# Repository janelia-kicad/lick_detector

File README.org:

# Created 2021-05-13 Thu 11:52
#+OPTIONS: title:nil author:nil email:nil toc:t |:t ^:nil
* Repository Information

- Name :: lick_detector
- Version :: 1.0
- License :: Open-Source Hardware
- URL :: https://github.com/janelia-kicad/lick_detector
- Author :: Peter Polidoro
- Email :: peter@polidoro.io

** Description

This board was designed to detect mouse licks using an accelerometer. The
board needs to be small and light weight and mounted to a lickport tube that
allows some small amount of motion.

* Images

* Schematic

[[file:./schematic/lick_detector.pdf][./schematic/lick_detector.pdf]]

[[file:./schematic/images/schematic00.png]]

* Gerbers

[[file:./gerbers/images/gerbers00.png]]

[[file:./gerbers/images/gerbers01.png]]

* Bill of Materials

** PCB Parts

| Item | Reference(s) | Quantity | Manufacturer       | Manufacturer Part Number | Vendor   | Vendor Part Number    | Description                  | Package |
|------+--------------+----------+--------------------+--------------------------+----------+-----------------------+------------------------------+---------|
|    1 | C1           |        1 | AVX Corporation    | TLCK106M006QTA           | Digi-Key | 478-5343-1-ND         | CAP TANT 10UF 20% 6.3V       |    0402 |
|    2 | C2 C3        |        2 | TDK Corporation    | C0603X5R1E104K030BB      | Digi-Key | 445-13671-1-ND        | CAP CER 0.1UF 25V X5R        |    0201 |
|    3 | P1           |        1 | Molex              | 5034800800               | Digi-Key | WM1388CT-ND           | CONN FFC FPC 8POS 0.50MM R/A |         |
|    4 | R1           |        1 | Yageo              | RC0201JR-0710RL          | Digi-Key | 311-10NCT-ND          | RES SMD 10 OHM 5% 1/20W      |    0201 |
|    5 | U1           |        1 | Analog Devices Inc | ADXL313WACPZ-RL7         | Digi-Key | ADXL313WACPZ-RL7CT-ND | ACCEL 0.5-4G I2C/SPI 32LFCSP |         |
|      | FID1         |        1 |                    |                          |          |                       |                              |         |

** Supplemental Parts

| Item | Quantity | Manufacturer | Manufacturer Part Number | Vendor   | Vendor Part Number | Description                  |
|------+----------+--------------+--------------------------+----------+--------------------+------------------------------|
|    1 |        1 | Molex        |               0150200073 | Digi-Key | 0150200073-ND      | CABLE FFC 8POS 0.50MM 1.18in |
|    2 |        1 | Molex        |               0150200075 | Digi-Key | WM11389-ND         | CABLE FFC 8POS 0.50MM 2in    |
|    3 |        1 | Molex        |               0150200077 | Digi-Key | 0150200077-ND      | CABLE FFC 8POS 0.50MM 3in    |
|    4 |        1 | Molex        |               0150200079 | Digi-Key | WM11395-ND         | CABLE FFC 8POS 0.50MM 4in    |
|    5 |        1 | Molex        |               0150200081 | Digi-Key | 0150200081-ND      | CABLE FFC 8POS 0.50MM 5in    |
|    6 |        1 | Molex        |               0150200083 | Digi-Key | WM6662-ND          | CABLE FFC 8POS 0.50MM 6in    |
|    7 |        1 | Molex        |               0150200087 | Digi-Key | WM11411-ND         | CABLE FFC 8POS 0.50MM 8in    |
|    8 |        1 | Molex        |               0150200093 | Digi-Key | WM25022-ND         | CABLE FFC 8POS 0.50MM 12in   |
#+TBLFM: $1=@#-1

** Vendor Parts Lists

[[file:./bom/Digi-Key_parts.csv][./bom/Digi-Key_parts.csv]]

* Supplemental Documentation

** Assembly Instructions

- Solder surface mount components onto the pcb.

* Manufacturing Archive

Send manufacturing zip file to your favorite PCB manufacturer for fabrication.

[[file:./manufacturing/lick_detector_v1.0.zip][./manufacturing/lick_detector_v1.0.zip]]

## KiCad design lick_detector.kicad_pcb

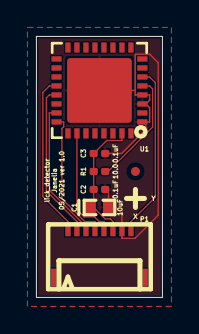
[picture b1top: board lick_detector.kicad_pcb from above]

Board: 2 copper layers, 7.0 x 14.5 mm, 7 parts (0 on the bottom side), 9 nets.

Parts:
C1: 10uF; SM0402_POL
C2, C3: 0.1uF; SM0201
FID1: FIDUCIAL
P1: CONN_FFC_8_RA; Molex_FFC_1x8_P0.5mm_RA
R1: 10.0; SM0201
U1: ADXL313; LFCSP-32-1EP_5x5mm_P0.5mm_EP3.6x3.6mm

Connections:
/INT1: P1.1, U1.20
/INT2: P1.2, U1.21
/MISO: P1.3, U1.23
/MOSI: P1.4, U1.24
/SCK: P1.5, U1.26
/~CS: P1.8, U1.6
GND: C1.2, C2.2, C3.2, P1.7, U1.1, U1.3, U1.4, U1.33
unnamed: R1.2, U1.5
VAA: C1.1, C2.1, C3.1, P1.6, R1.1, U1.31

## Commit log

2021-04-30 Add ADXL313
2021-05-01 Add Pico-Clasp 8-pin
2021-05-03 Add Pico-Clasp component
2021-05-03 Add connector to schematic
2021-05-04 Add capacitors and receptacle
2021-05-04 Add 10.0_0402
2021-05-04 Add 10k
2021-05-05 Add BUFFER_TRI_STATE and BUFFER_2_ELEMENT
2021-05-06 Switch to flex cable
2021-05-07 Migrate toward 0201
2021-05-10 Rearrange pcb footprints
2021-05-10 Layout experimentation
2021-05-10 Auto routed layout
2021-05-12 Remove pin receptacle
2021-05-12 Rectangular outline
2021-05-12 Add all flex cable sizes to supplemental_bom
2021-05-13 Export supplementals
2021-05-13 Add generate_kicad_documentation submodule
2021-05-13 Generate documentation
2021-09-16 Update email address
2021-09-17 Update generate_kicad_documentation
2021-09-21 Remove ignored files
2022-02-22 Add guix files
2022-02-23 Add guix documentation
